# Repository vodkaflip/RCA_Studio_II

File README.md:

# RCA Studio II

## Multicart Hardware
The cartridge uses a 512k flash chip (SST39SF040) to provide 128 selectable 4k slots to the RCA Studio II Console. The cartridge has a latch circuit for the higher address lines. The original version of the multicart had a dual retriggerable monostable multi-vibrator (courtesy of Ed Keefe) to ‘repair’ the TPA line, which is crippled on most console cartridge ports. A jumper selects whether the cartridge generates this signal (bridge the top two pins of the jumper, default) or whether it uses the one generated by the console (bottom two pins). The latter is needed for some older versions of the Studio II and for the color clones.

The newer version (v5) of the multicart no longer needs the patch circuit: it mixes in the /MRD signal to generate working CE and OE for the EEPROM to work correctly. 

A switch selects whether $000-$3FF is addressable on the cartridge. This will bypass the console's roms/kernels so that Chip-8 games or alternative kernels can be used.

The Multicart PCB has provisions to replace the two hex encoders that select the ROM slot with a microview arduino. In combination with a single rotary dial, a slot can be selected an activated.

## Updating Multicart
If new ROMs become available, the flash memory on the cartridge can be updated to include these. Note that the entire image (512k) will probably need to be rewritten to the chip. This requires a programmer that supports the 39SF040 flash memory chip, which should be most devices. Since the chip is a PLCC32 package, an adapter is probably needed. Check the AtariAge forums for news and help if needed.

### SLOT STRUCTURE (4096 bytes)
```
$xy000-$xy3FF	KERNEL
$xy400-$xy7FF	Low ROM area
$xy800-$xyBFF	[not used by cart - console RAM]
$xyC00-$xyFFF	High ROM area

where	x = high bank select (MSB)
	    y = low bank select (LSB)
```

See the readme in the eeprom directory for more details on how the eeprom image can be 'compiled'.

## Single cart Hardware
This is very similar to the multicart design, apart from the slot selection rotary encoders. And it uses a much smaller eprom: 2716 or 2732 - this needs to be set via a jumper. A switch (or jumper) can determine whether the console uses $000-$3ff from the cartridge or from the console. It allows different kernels to be run from the cart (e.g. Chip-8 games).

## CARTRIDGE SLOT
Since the cartridge slot is unprotected on this 40 year old console, corrosion of the contacts is very likely. This will hamper correct operation of the cartridge and is a likely source of problems/crashes you may experience. If that’s the case, please ensure that the cartridge slot pins on the back row are clean. Use contact cleaner or similar if necessary.

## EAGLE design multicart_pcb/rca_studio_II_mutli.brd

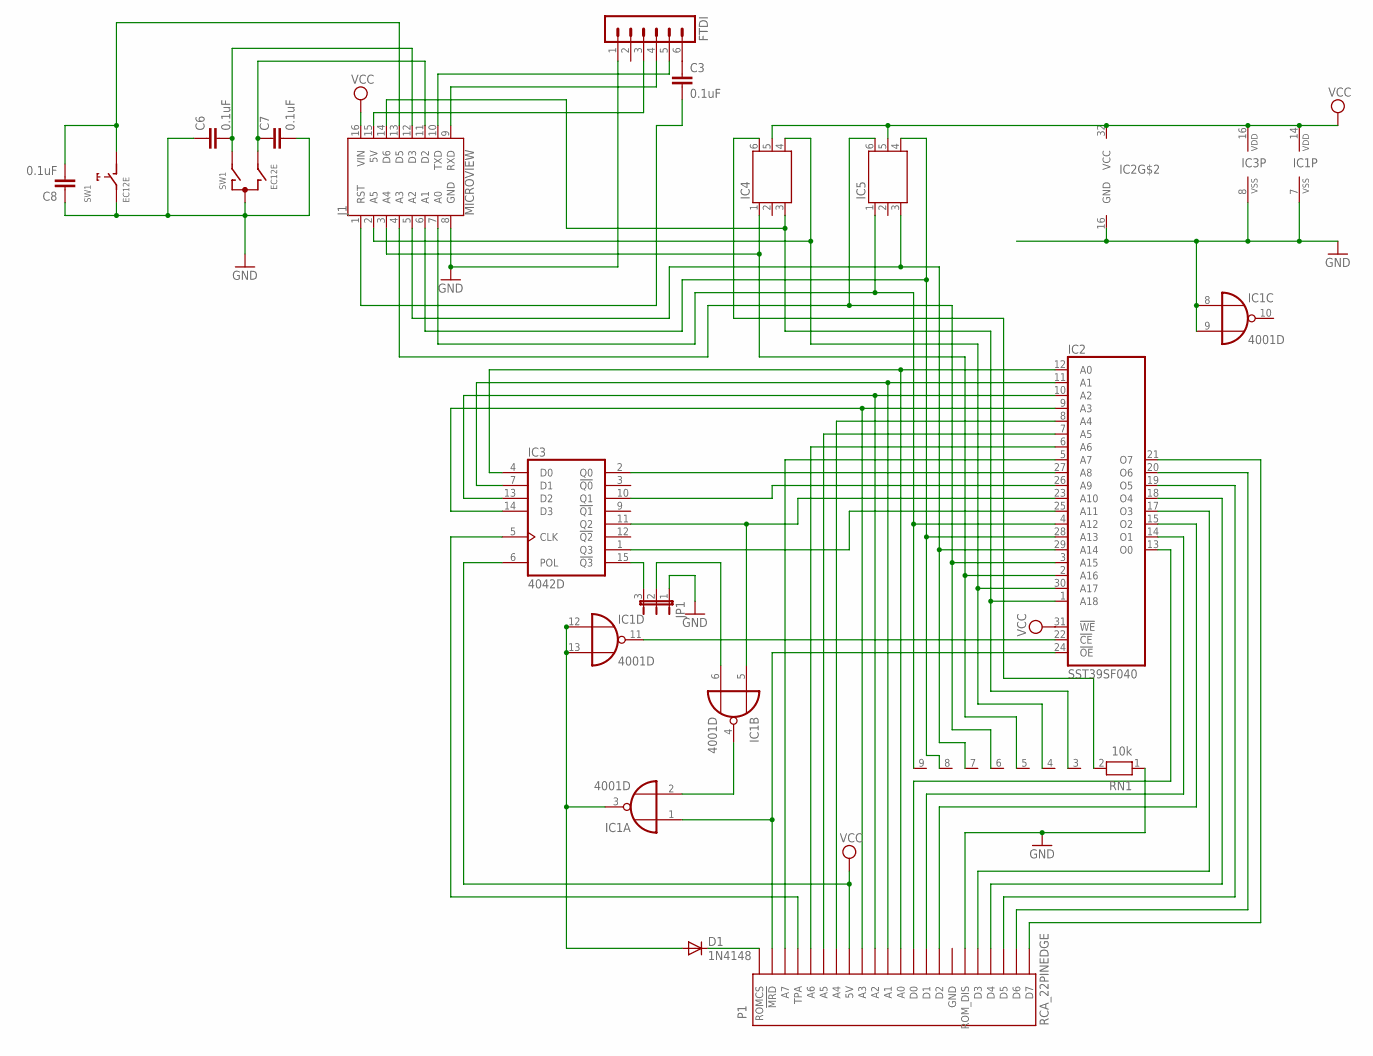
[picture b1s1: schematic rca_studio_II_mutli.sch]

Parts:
C3, C6, C7, C8: 0.1uF; C0805
D1: 1N4148; DO35-7
FTDI: MA06-1
IC1: 4001D; SO14
IC2: SST39SF040; S32
IC3: 4042D; SO16
IC4, IC5: HEXENCODERHEXENCODER; HEXENCODER
J1: MICROVIEW; MV-DIP16-NODIMENSION
JP1: JP2E; JP2
P1: RCA_22PINEDGE
RN1: 10k; RN-9
SW1: EC12E; ALPS_EC12E_SW

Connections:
A0: IC2.12 (A0), IC3.4 (D0), P1.11 (A0)
A1: IC2.11 (A1), IC3.7 (D1), P1.12 (A1)
A2: IC2.10 (A2), IC3.13 (D2), P1.13 (A2)
A3: IC2.9 (A3), IC3.14 (D3), P1.14 (A3)
A4: IC2.8 (A4), P1.16 (A4)
A5: IC2.7 (A5), P1.17 (A5)
A6: IC2.6 (A6), P1.18 (A6)
A7: IC2.5 (A7), P1.20 (A7)
A8: IC2.27 (A8), IC3.2 (Q0)
A9: IC2.26 (A9), IC3.10 (Q1)
A10: IC1.5 (I0), IC2.23 (A10), IC3.11 (Q2)
A11: IC2.25 (A11), IC3.1 (Q3)
A12: IC2.4 (A12), IC5.1, J1.7 (A0), RN1.9
A13: IC2.28 (A13), IC5.4 (2), J1.6 (A1), RN1.8
A14: IC2.29 (A14), IC5.3 (4), J1.5 (A2), RN1.7
A15: IC2.3 (A15), IC5.6 (8), J1.4 (A3), RN1.6
A16: IC2.2 (A16), IC4.1, J1.3 (A4), RN1.5
A17: IC2.30 (A17), IC4.4 (2), J1.2 (A5), RN1.4
A18: IC2.1 (A18), IC4.3 (4), J1.14 (D6), RN1.3
GND: C6.1, C7.2, C8.1, FTDI.1, IC1.7 (VSS), IC1.8 (I0), IC1.9 (I1), IC2.16 (GND), IC3.8 (VSS), J1.8 (GND), JP1.1, P1.6 (ROM_DIS), RN1.1, SW1.C, SW1.E (2)
unnamed: IC1.11 (O), IC2.22 (!CE)
unnamed: IC2.21 (O7), P1.1 (D7)
unnamed: IC2.20 (O6), P1.2 (D6)
unnamed: IC2.19 (O5), P1.3 (D5)
unnamed: IC2.18 (O4), P1.4 (D4)
unnamed: IC2.17 (O3), P1.5 (D3)
unnamed: IC2.15 (O2), P1.8 (D2)
unnamed: IC2.14 (O1), P1.9 (D1)
unnamed: IC2.13 (O0), P1.10 (D0)
unnamed: C6.2, J1.12 (D3), SW1.A
unnamed: IC1.1 (I0), IC2.24 (!OE), P1.21 (!MRD)
unnamed: C7.1, J1.11 (D2), SW1.B
unnamed: IC1.2 (I1), IC1.4 (O)
unnamed: D1.A, IC1.3 (O), IC1.12 (I0), IC1.13 (I1)
unnamed: C8.2, J1.13 (D5), SW1.D (1)
unnamed: IC3.15 (!Q3), JP1.3
unnamed: FTDI.3, J1.15 (5V)
unnamed: FTDI.4, J1.9 (RXD)
unnamed: FTDI.5, J1.10 (TXD)
unnamed: C3.2, J1.1 (RST)
unnamed: C3.1, FTDI.6
unnamed: IC1.6 (I1), JP1.2
unnamed: D1.C, P1.22 (ROMCS)
unnamed: IC4.6 (8), RN1.2
unnamed: IC3.5 (CLK), P1.19 (TPA)
VCC: IC1.14 (VDD), IC2.31 (!WE), IC2.32 (VCC), IC3.6 (POL), IC3.16 (VDD), IC4.5 (C2), IC5.5 (C2), J1.16 (VIN), P1.15 (5V)

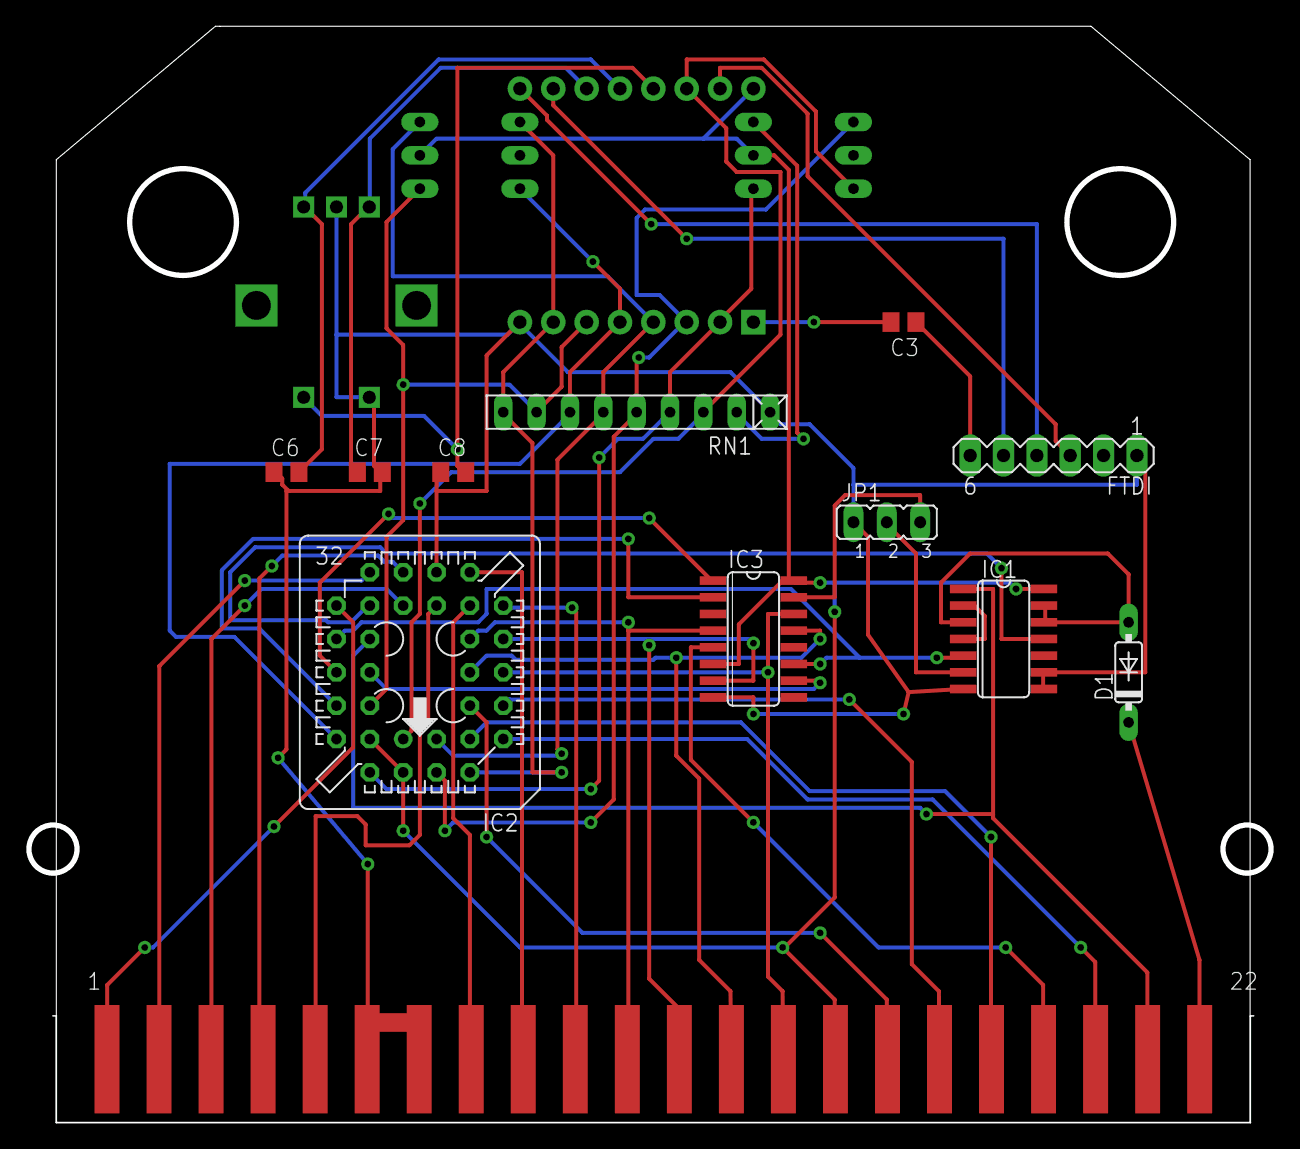
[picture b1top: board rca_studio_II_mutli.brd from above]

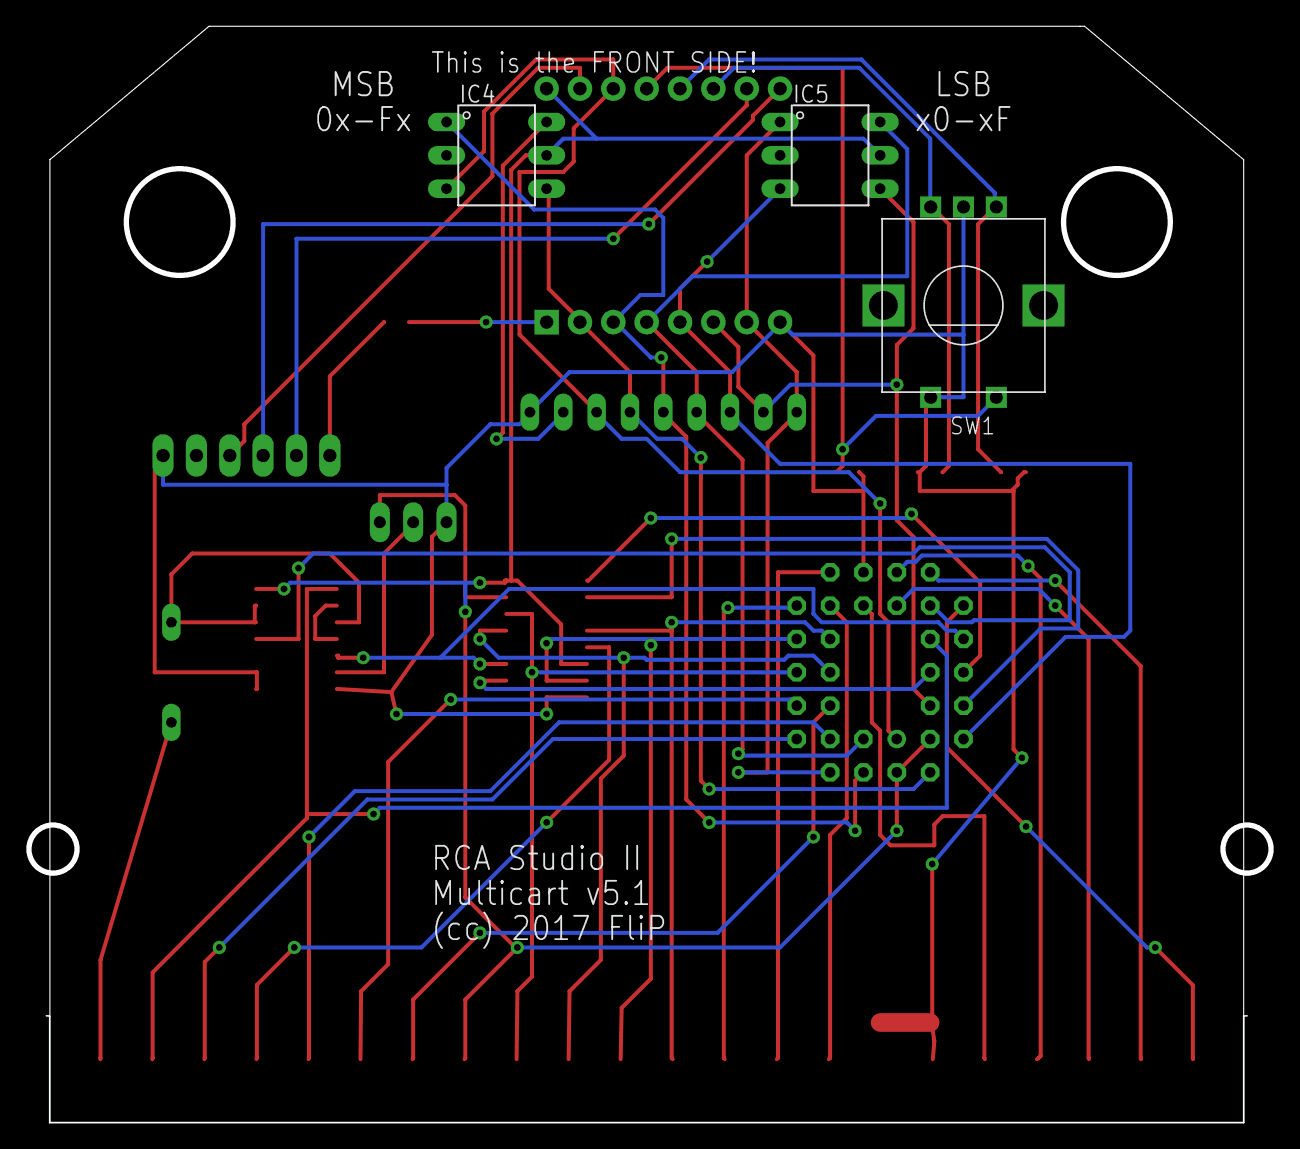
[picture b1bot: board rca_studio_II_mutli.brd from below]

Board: 2 copper layers, 94.6 x 83.1 mm, 16 parts (4 on the bottom side), 46 nets.

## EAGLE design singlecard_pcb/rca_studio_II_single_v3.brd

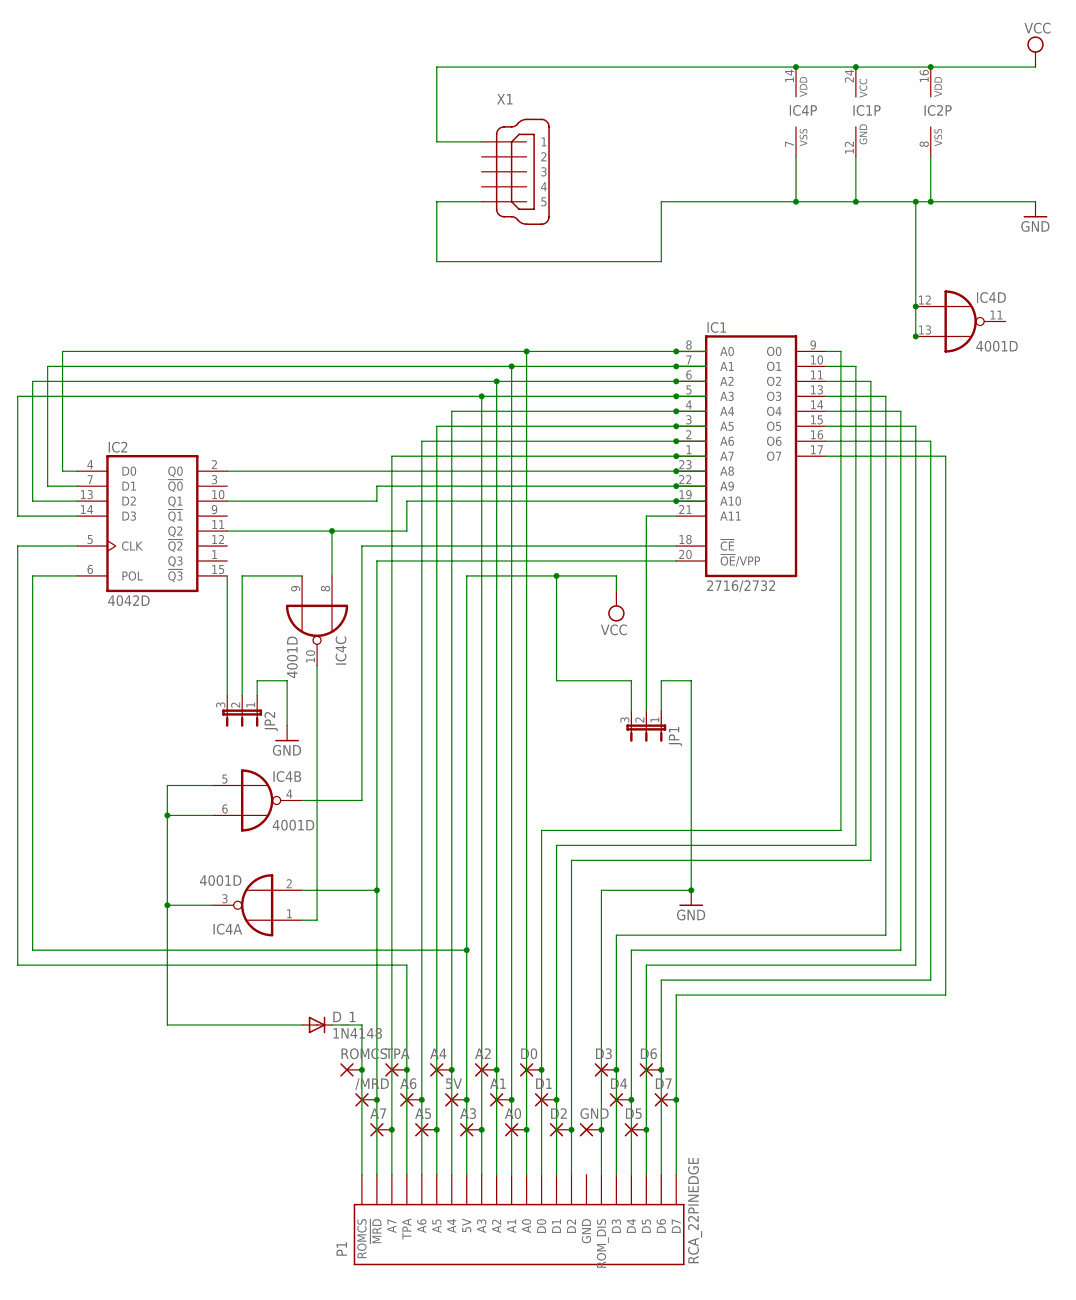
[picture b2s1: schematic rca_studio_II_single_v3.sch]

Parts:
5V: WIREPAD2,15/1,0; 2,15/1,0
/MRD: WIREPAD2,15/1,0; 2,15/1,0
A0, A1, A2, A3, A4, A5, A6, A7: WIREPAD2,15/1,0; 2,15/1,0
D0, D1, D2, D3, D4, D5, D6, D7: WIREPAD2,15/1,0; 2,15/1,0
D_1: 1N4148; DO35-7
GND: WIREPAD2,15/1,0; 2,15/1,0
IC1: 2716/2732; DIL24
IC2: 4042D; SO16
IC4: 4001D; SO14
JP1, JP2: JP2E; JP2
P1: RCA_22PINEDGE
ROMCS: WIREPAD2,15/1,0; 2,15/1,0
TPA: WIREPAD2,15/1,0; 2,15/1,0
X1: MINI-USB-32005-301; 32005-301

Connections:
01: D1.1, IC1.10 (O1), P1.9 (D1)
/MRD: /MRD.1, IC1.20 (!OE!/VPP), IC4.2 (I1), P1.21 (!MRD)
A0: A0.1, IC1.8 (A0), IC2.4 (D0), P1.11 (A0)
A1: A1.1, IC1.7 (A1), IC2.7 (D1), P1.12 (A1)
A2: A2.1, IC1.6 (A2), IC2.13 (D2), P1.13 (A2)
A3: A3.1, IC1.5 (A3), IC2.14 (D3), P1.14 (A3)
A4: A4.1, IC1.4 (A4), P1.16 (A4)
A5: A5.1, IC1.3 (A5), P1.17 (A5)
A6: A6.1, IC1.2 (A6), P1.18 (A6)
A7: A7.1, IC1.1 (A7), P1.20 (A7)
A8: IC1.23 (A8), IC2.2 (Q0)
A9: IC1.22 (A9), IC2.10 (Q1)
A10: IC1.19 (A10), IC2.11 (Q2), IC4.8 (I0)
A11: IC1.21 (A11), JP1.2
D0: D0.1, IC1.9 (O0), P1.10 (D0)
D2: D2.1, IC1.11 (O2), P1.8 (D2)
D3: D3.1, IC1.13 (O3), P1.5 (D3)
D4: D4.1, IC1.14 (O4), P1.4 (D4)
D5: D5.1, IC1.15 (O5), P1.3 (D5)
D6: D6.1, IC1.16 (O6), P1.2 (D6)
D7: D7.1, IC1.17 (O7), P1.1 (D7)
GND: GND.1, IC1.12 (GND), IC2.8 (VSS), IC4.7 (VSS), IC4.12 (I0), IC4.13 (I1), JP1.1, JP2.1, P1.6 (ROM_DIS), X1.5
unnamed: IC4.1 (I0), IC4.10 (O)
unnamed: IC4.9 (I1), JP2.2
unnamed: IC1.18 (!CE), IC4.4 (O)
unnamed: D_1.A, IC4.3 (O), IC4.5 (I0), IC4.6 (I1)
unnamed: IC2.15 (!Q3), JP2.3
ROMCS: D_1.C, P1.22 (ROMCS), ROMCS.1
TPA: IC2.5 (CLK), P1.19 (TPA), TPA.1
VCC: 5V.1, IC1.24 (VCC), IC2.6 (POL), IC2.16 (VDD), IC4.14 (VDD), JP1.3, P1.15 (5V), X1.1

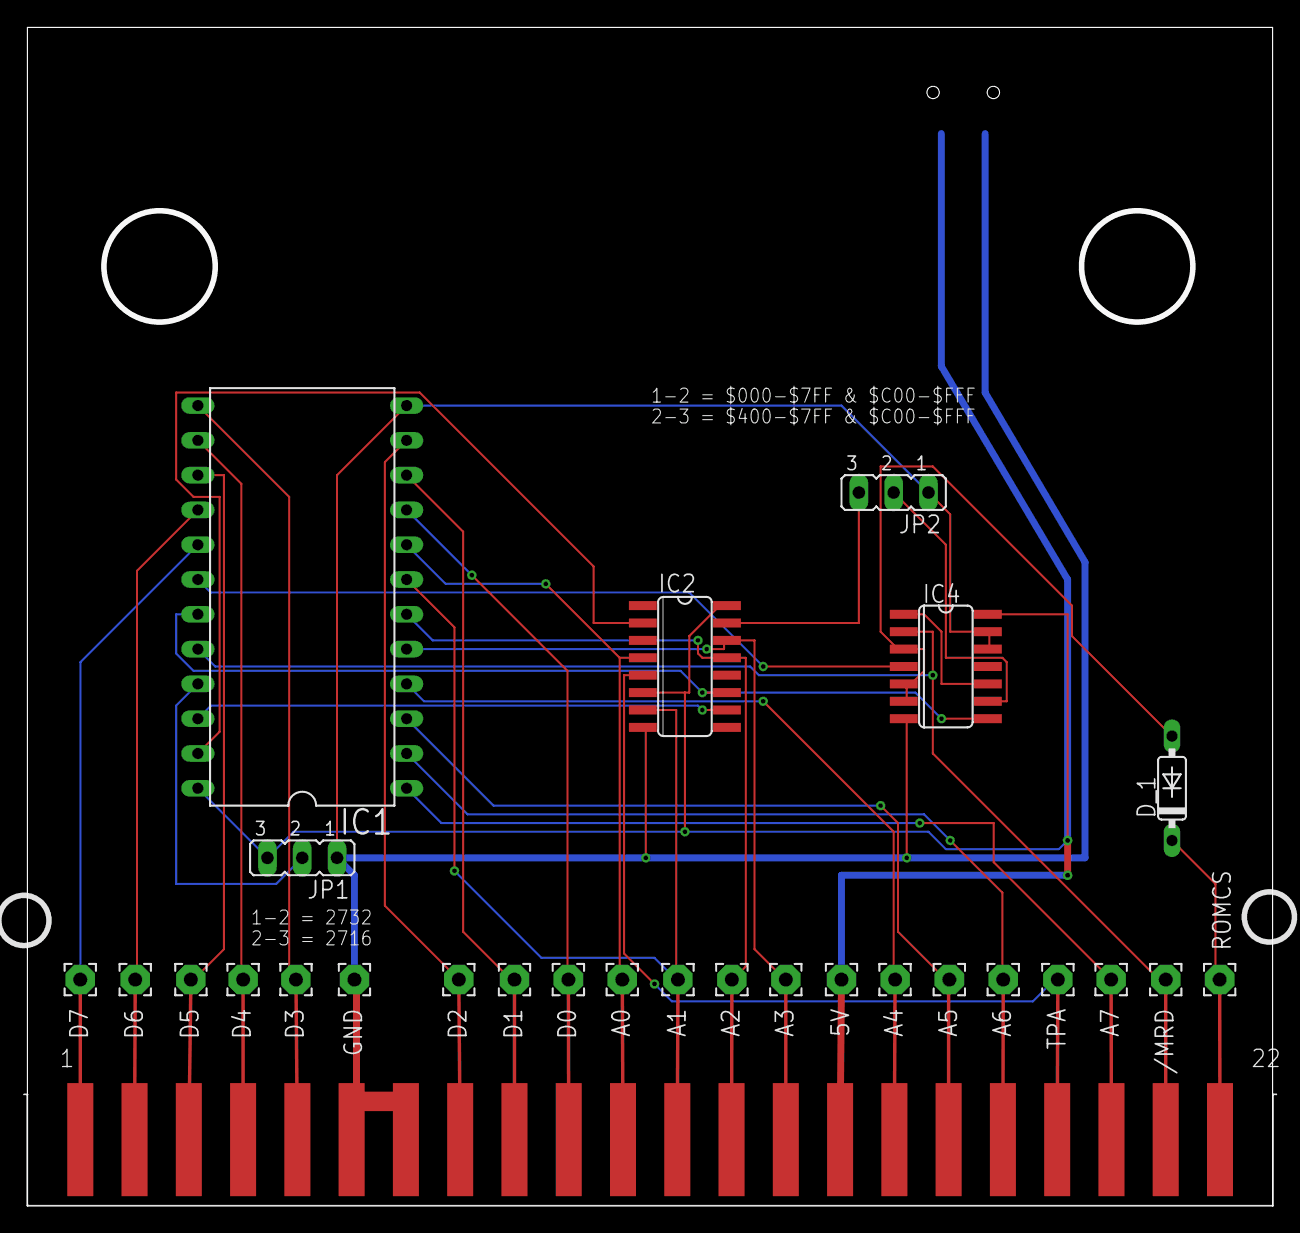
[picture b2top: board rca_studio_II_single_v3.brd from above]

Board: 2 copper layers, 90.5 x 85.6 mm, 29 parts (1 on the bottom side), 30 nets.

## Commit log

2018-05-27 Initial upload
2019-06-09 Rename readme.txt to readme.md
2022-01-28 multicart v5.1
